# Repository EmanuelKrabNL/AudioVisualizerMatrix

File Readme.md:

# Audio Visualizer
i added matrix cuz that sounds cooler

## What does it do?
Its an audio visualizer (duh), except it shows in waves, with dots, build on the max 7219 (4 in one) led matrix.

## Features
well, it displays the audio of your pc in like, dots or something...

## But what does it look like?

Schematic

PCB

## Why have i made it?
Because i have always wanted it, but i especially made it for the hack club half life program!

## How does it work?
You plug in the pcb, run the script and voila: it displays your audio!

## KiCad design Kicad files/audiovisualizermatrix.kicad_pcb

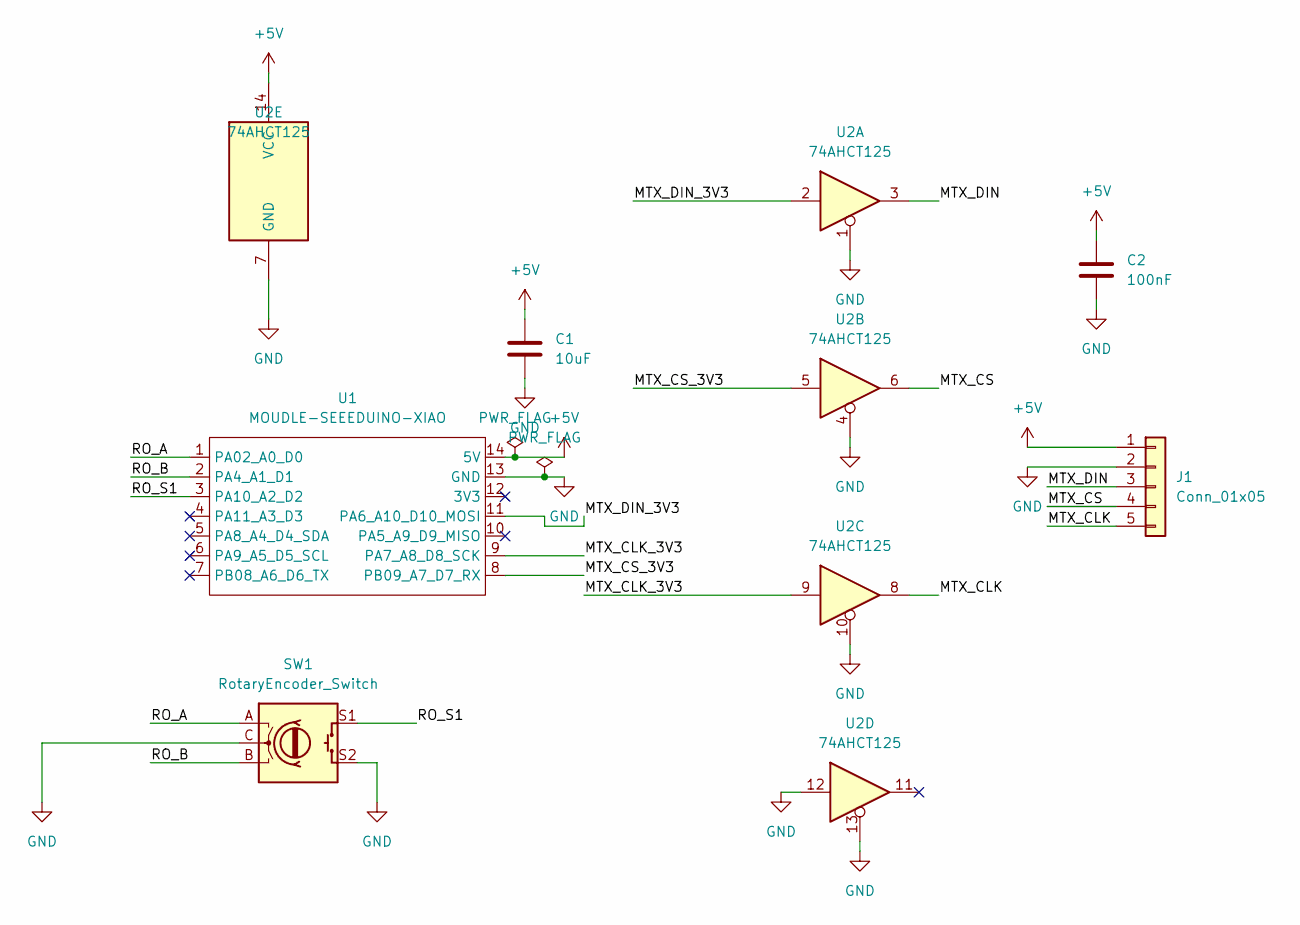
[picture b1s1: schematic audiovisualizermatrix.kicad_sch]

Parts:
C1: 10uF; C_0805_2012Metric
C2: 100nF; C_0805_2012Metric
J1: Conn_01x05; PinSocket_1x05_P2.54mm_Vertical
SW1: RotaryEncoder_Switch; RotaryEncoder_Alps_EC11E-Switch_Vertical_H20mm
U1: MOUDLE-SEEEDUINO-XIAO; XIAO-Generic-Hybrid-14P-2.54-21X17.8MM
U2: 74AHCT125; SOIC-14_3.9x8.7mm_P1.27mm

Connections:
+5V: C1.1, C2.1, J1.1, U1.14 (5V), U2.14 (VCC)
/MTX_CLK: J1.5, U2.8
/MTX_CLK_3V3: U1.9 (PA7_A8_D8_SCK), U2.9
/MTX_CS: J1.4, U2.6
/MTX_CS_3V3: U1.8 (PB09_A7_D7_RX), U2.5
/MTX_DIN: J1.3, U2.3
/MTX_DIN_3V3: U1.11 (PA6_A10_D10_MOSI), U2.2
/RO_A: SW1.A, U1.1 (PA02_A0_D0)
/RO_B: SW1.B, U1.2 (PA4_A1_D1)
/RO_S1: SW1.S1, U1.3 (PA10_A2_D2)
GND: C1.2, C2.2, J1.2, SW1.C, SW1.S2, U1.13 (GND), U2.1, U2.4, U2.7 (GND), U2.10, U2.12, U2.13

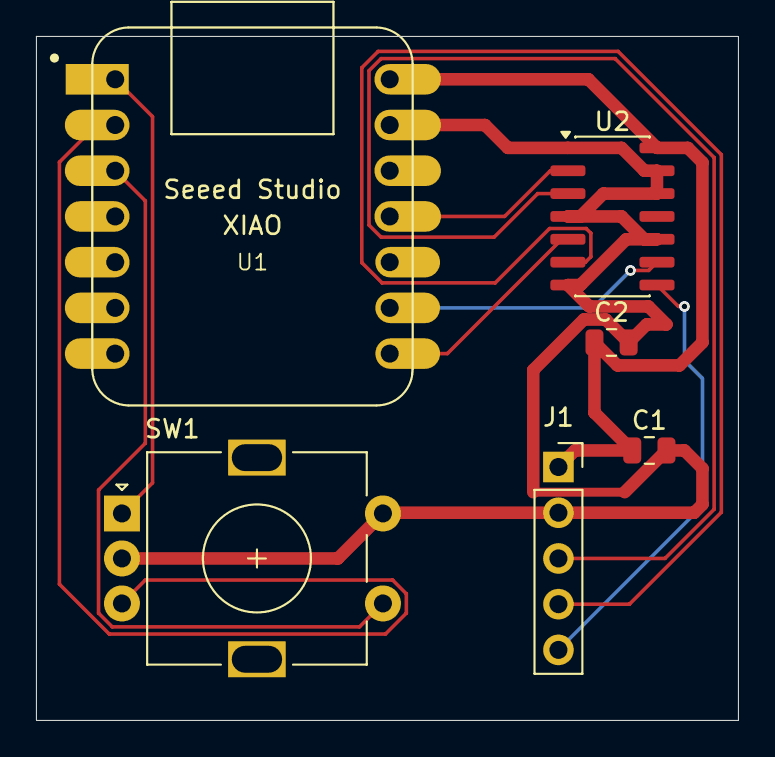
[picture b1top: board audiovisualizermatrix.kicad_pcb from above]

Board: 2 copper layers, 39.0 x 38.0 mm, 6 parts (0 on the bottom side), 11 nets.

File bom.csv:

Designator,Footprint,Quantity,Value,LCSC Part #
C1,0805,1,10uF,
C2,0805,1,100nF,
J1,PinSocket_1x05_P2.54mm_Vertical,1,Conn_01x05,
SW1,RotaryEncoder_Alps_EC11E-Switch_Vertical_H20mm,1,RotaryEncoder_Switch,
U1,XIAO-Generic-Hybrid-14P-2.54-21X17.8MM,1,MOUDLE-SEEEDUINO-XIAO,
U2,SOIC-14_3.9x8.7mm_P1.27mm,1,74AHCT125,
